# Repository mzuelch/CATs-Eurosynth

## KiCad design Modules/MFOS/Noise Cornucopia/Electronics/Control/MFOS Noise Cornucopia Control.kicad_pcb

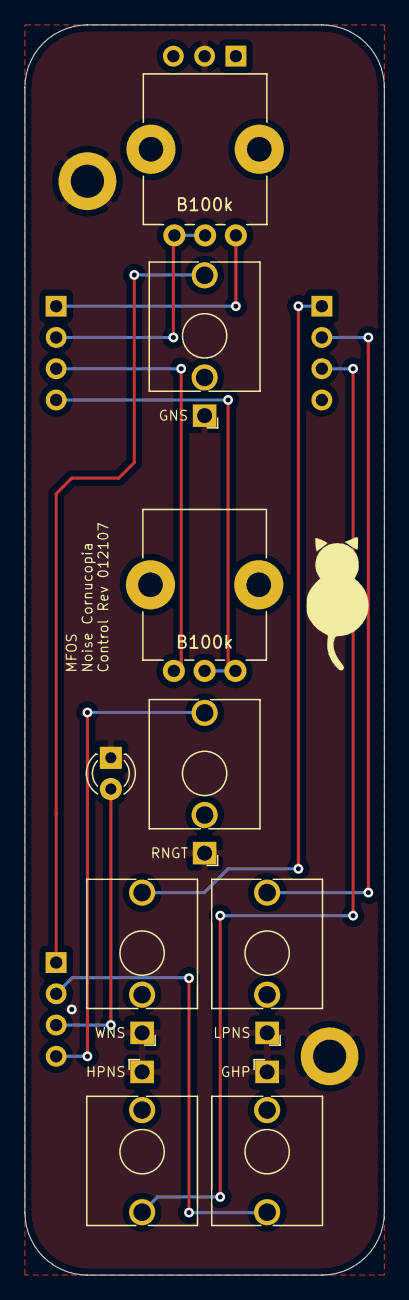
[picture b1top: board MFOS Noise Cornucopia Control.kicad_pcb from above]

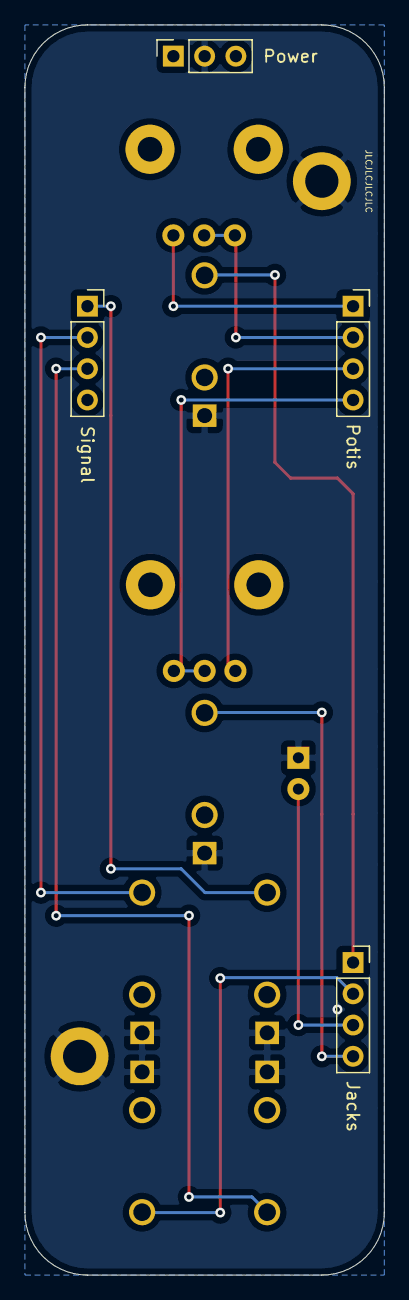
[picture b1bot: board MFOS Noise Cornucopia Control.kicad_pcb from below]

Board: 2 copper layers, 29.2 x 101.6 mm, 15 parts (4 on the bottom side), 12 nets.

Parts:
D1: LED; LED_D3.0mm
H1, H2: MountingHole_Pad; MountingHole_2.7mm_M2.5_DIN965_Pad
J1: WNS; Jack_3.5mm_QingPu_WQP-PJ398SM_Vertical_CircularHoles
J2: Power; PinSocket_1x03_P2.54mm_Vertical
J3: Signal; PinSocket_1x04_P2.54mm_Vertical
J4: LPNS; Jack_3.5mm_QingPu_WQP-PJ398SM_Vertical_CircularHoles
J5: HPNS; Jack_3.5mm_QingPu_WQP-PJ398SM_Vertical_CircularHoles
J6: Potis; PinSocket_1x04_P2.54mm_Vertical
J7: Jacks; PinSocket_1x04_P2.54mm_Vertical
J8: GNS; Jack_3.5mm_QingPu_WQP-PJ398SM_Vertical_CircularHoles
J9: GHP; Jack_3.5mm_QingPu_WQP-PJ398SM_Vertical_CircularHoles
J10: RNGT; Jack_3.5mm_QingPu_WQP-PJ398SM_Vertical_CircularHoles
R18, R28: B100k; Potentiometer_Alps_RK09K_Single_Vertical

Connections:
GHP: J7.2, J9.T
GND: D1.1, H1.1, H2.1, J1.S, J2.2, J4.S, J5.S, J8.S, J9.S, J10.S
GNS: J7.1, J8.T
GRNS1: J6.1, R18.1
GRNS2: J6.2, R18.2, R18.3
GTF1: J6.3, R28.3
GTF2: J6.4, R28.1, R28.2
HPNS: J3.3, J5.T
LEDA: D1.2, J7.3
LPNS: J3.2, J4.T
RNGT: J7.4, J10.T
WNS: J1.T, J3.1

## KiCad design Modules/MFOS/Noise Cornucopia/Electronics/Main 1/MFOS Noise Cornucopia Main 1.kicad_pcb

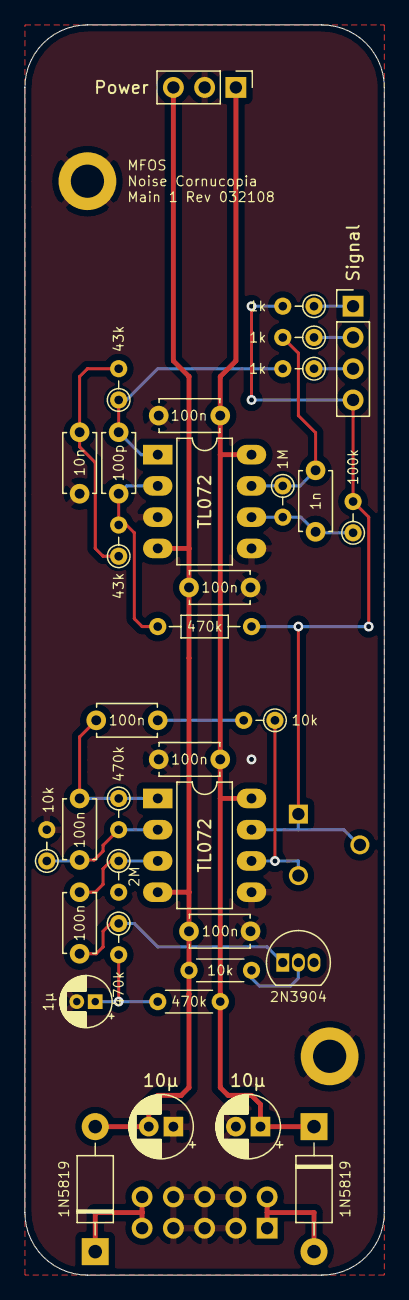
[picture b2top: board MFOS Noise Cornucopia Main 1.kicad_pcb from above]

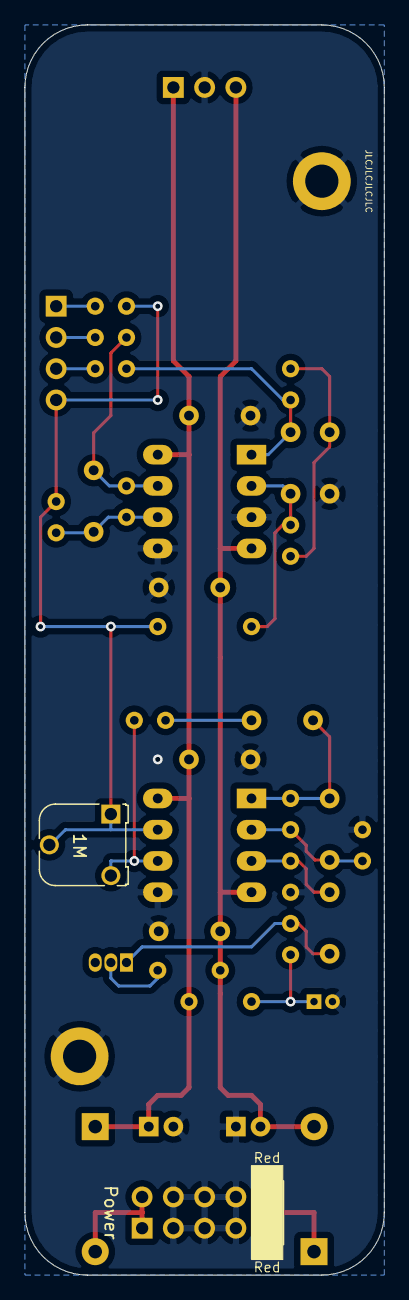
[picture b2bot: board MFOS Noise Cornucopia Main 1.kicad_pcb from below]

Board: 2 copper layers, 29.2 x 101.6 mm, 39 parts (2 on the bottom side), 22 nets.

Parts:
C1, C2, C4, C5, C7, C10, C12: 100n; C_Disc_D4.7mm_W2.5mm_P5.00mm
C3: 1n; C_Disc_D4.7mm_W2.5mm_P5.00mm
C6, C11: 10µ; CP_Radial_D5.0mm_P2.00mm
C9: 100p; C_Disc_D4.7mm_W2.5mm_P5.00mm
C14: 10n; C_Disc_D4.7mm_W2.5mm_P5.00mm
C18: 1µ; CP_Radial_D4.0mm_P1.50mm
D4, D5: 1N5819; D_DO-41_SOD81_P10.16mm_Horizontal
H1, H2: MountingHole_Pad; MountingHole_2.7mm_M2.5_DIN965_Pad
J1: Signal; PinHeader_1x04_P2.54mm_Vertical
J2: Power; PinHeader_1x03_P2.54mm_Vertical
J4: Power; Power_2x5_Vertical
Q1: 2N3904; TO-92_Inline
R1, R3, R11: 1k; R_Axial_DIN0204_L3.6mm_D1.6mm_P2.54mm_Vertical
R2, R10: 470k; R_Axial_DIN0204_L3.6mm_D1.6mm_P2.54mm_Vertical
R4: 2M; R_Axial_DIN0204_L3.6mm_D1.6mm_P2.54mm_Vertical
R5, R9: 10k; R_Axial_DIN0204_L3.6mm_D1.6mm_P2.54mm_Vertical
R6: 100k; R_Axial_DIN0204_L3.6mm_D1.6mm_P2.54mm_Vertical
R7: 1M; R_Axial_DIN0204_L3.6mm_D1.6mm_P2.54mm_Vertical
R8: 1M; Potentiometer_Runtron_RM-065_Vertical
R12: 470k; R_Axial_DIN0204_L3.6mm_D1.6mm_P7.62mm_Horizontal
R16, R17: 43k; R_Axial_DIN0204_L3.6mm_D1.6mm_P2.54mm_Vertical
R33: 470k; R_Axial_DIN0204_L3.6mm_D1.6mm_P5.08mm_Horizontal
R34: 10k; R_Axial_DIN0204_L3.6mm_D1.6mm_P5.08mm_Horizontal
U1, U2: TL072; DIP-8_W7.62mm_LongPads

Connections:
+12V: C5.2, C6.1, C7.2, D4.1, J2.1, R33.1, U1.8, U2.8
+12VA: D4.2, J4.+12V
-12V: C10.1, C11.2, C12.1, D5.2, J2.3, R34.2, U1.4, U2.4
-12VA: D5.1, J4.-12V
GND: C5.1, C6.2, C7.1, C10.2, C11.1, C12.2, C14.1, C18.2, H1.1, H2.1, J2.2, J4.GND, R4.2, R9.2, U1.5, U2.3, U2.5
HPNS: J1.3, R11.1
LPNS: J1.2, R3.1
NOISE_INT: J1.4, R1.2, R6.2, R8.1, R8.2, R12.2, U1.7
unnamed: C1.1, R4.1, U1.3
unnamed: C1.2, Q1.1, R2.1
unnamed: C2.1, R5.2
unnamed: C2.2, C4.1, R10.1, U1.1
unnamed: C3.1, R3.2, R7.1, U2.7
unnamed: C3.2, R6.1, R7.2, U2.6
unnamed: C4.2, R9.1, R10.2, U1.2
unnamed: C9.1, R12.1, R16.2, U2.2
unnamed: C9.2, R11.2, R17.1, U2.1
unnamed: C14.2, R16.1, R17.2
unnamed: C18.1, R2.2, R33.2
unnamed: Q1.2, R34.1
unnamed: R5.1, R8.3, U1.6
WNS: J1.1, R1.1

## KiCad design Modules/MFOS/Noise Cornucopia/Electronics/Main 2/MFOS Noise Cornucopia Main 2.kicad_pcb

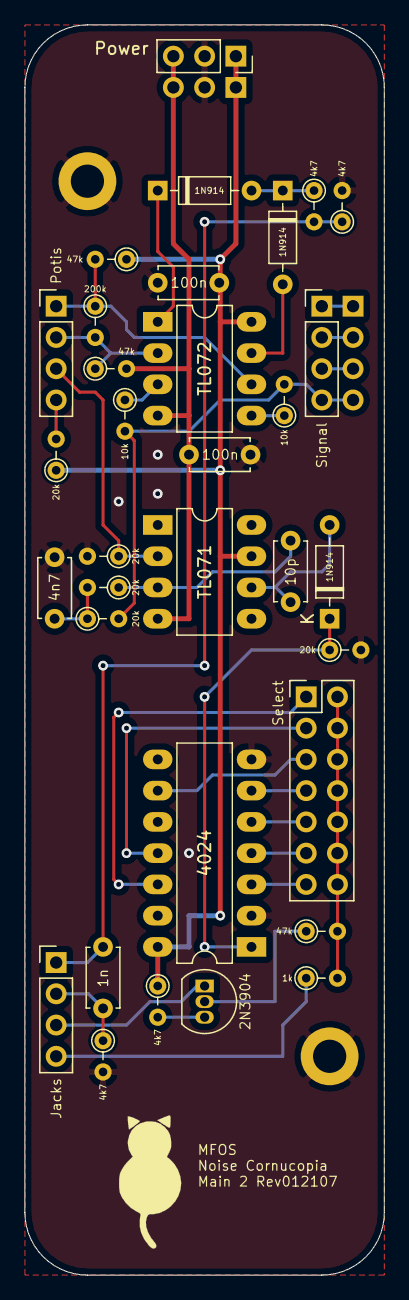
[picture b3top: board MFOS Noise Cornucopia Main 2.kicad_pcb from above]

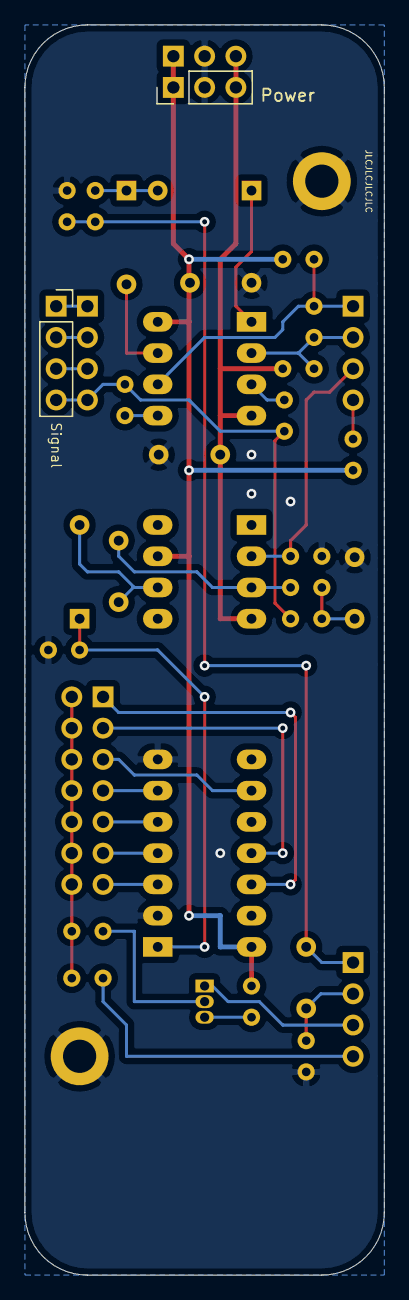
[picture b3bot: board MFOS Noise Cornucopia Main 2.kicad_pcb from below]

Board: 2 copper layers, 29.2 x 101.6 mm, 37 parts (2 on the bottom side), 34 nets.

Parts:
C8, C13: 100n; C_Disc_D4.7mm_W2.5mm_P5.00mm
C15: 1n; C_Disc_D4.7mm_W2.5mm_P5.00mm
C16: 10p; C_Disc_D4.7mm_W2.5mm_P5.00mm
C17: 4n7; C_Disc_D4.7mm_W2.5mm_P5.00mm
D1, D2, D3: 1N914; D_DO-35_SOD27_P7.62mm_Horizontal
H1, H2: MountingHole_Pad; MountingHole_2.7mm_M2.5_DIN965_Pad
J1: Select; PinHeader_2x07_P2.54mm_Vertical
J2: Power; PinSocket_1x03_P2.54mm_Vertical
J3: Signal; PinSocket_1x04_P2.54mm_Vertical
J4: Signal; PinHeader_1x04_P2.54mm_Vertical
J5: Power; PinHeader_1x03_P2.54mm_Vertical
J6: Potis; PinHeader_1x04_P2.54mm_Vertical
J7: Jacks; PinHeader_1x04_P2.54mm_Vertical
Q2: 2N3904; TO-92_Inline
R13, R22, R30: 47k; R_Axial_DIN0204_L3.6mm_D1.6mm_P2.54mm_Vertical
R14, R20: 10k; R_Axial_DIN0204_L3.6mm_D1.6mm_P2.54mm_Vertical
R15, R21, R23, R24: 4k7; R_Axial_DIN0204_L3.6mm_D1.6mm_P2.54mm_Vertical
R19: 200k; R_Axial_DIN0204_L3.6mm_D1.6mm_P2.54mm_Vertical
R25, R26, R27, R29, R31: 20k; R_Axial_DIN0204_L3.6mm_D1.6mm_P2.54mm_Vertical
R32: 1k; R_Axial_DIN0204_L3.6mm_D1.6mm_P2.54mm_Vertical
U3: TL072; DIP-8_W7.62mm_LongPads
U4: TL071; DIP-8_W7.62mm_LongPads
U5: 4024; DIP-14_W7.62mm_LongPads

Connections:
+12V: C8.2, J2.1, J5.1, R13.1, R24.1, R25.1, U3.8, U4.7, U5.14
-12V: C13.1, J2.3, J5.3, R22.2, U3.4, U4.4
GHP: C15.2, J7.2, R23.1
GND: C8.1, C13.2, C17.2, H1.1, H2.1, J2.2, J5.2, R21.2, R23.2, R29.2, R31.2, U5.2, U5.7
GNS: C15.1, J7.1, R15.2, R21.1
GRNS1: J6.1, R13.2, R19.1, U3.6
GRNS2: J6.2, R19.2, R22.1, U3.2
GTF1: J6.3, R31.1, U4.2
GTF2: J6.4, R25.2
LEDA: J7.3, Q2.1
NOISE_INT: J3.4, J4.4, R14.2, R20.2, R26.2
unnamed: C16.1, R27.1, U4.3
unnamed: C16.2, D3.2, U4.6
unnamed: C17.1, R26.1, R27.2
unnamed: D1.1, D2.2, R15.1
unnamed: D1.2, U3.7
unnamed: D2.1, U3.1
unnamed: D3.1, R29.1, U5.1
unnamed: J1.1, U5.12
unnamed: J1.3, U5.11
unnamed: J1.5, U5.9
unnamed: J1.7, U5.6
unnamed: J1.9, U5.5
unnamed: J1.2, J1.4, J1.6, J1.8, J1.10, J1.12, J1.14, R30.2, R32.2
unnamed: J1.11, U5.4
unnamed: J1.13, U5.3
unnamed: J3.1, J4.1
unnamed: J3.2, J4.2
unnamed: J3.3, J4.3
unnamed: Q2.2, R30.1
unnamed: Q2.3, R24.2
unnamed: R14.1, U3.5
unnamed: R20.1, U3.3
RNGT: J7.4, R32.1

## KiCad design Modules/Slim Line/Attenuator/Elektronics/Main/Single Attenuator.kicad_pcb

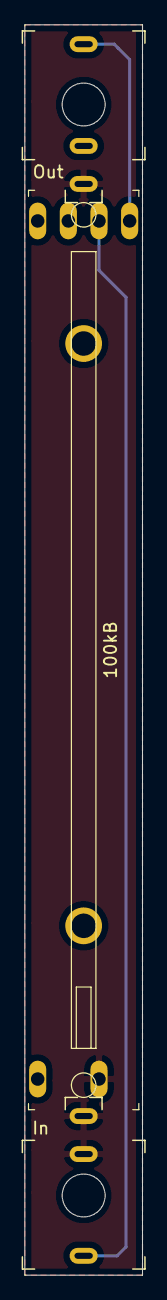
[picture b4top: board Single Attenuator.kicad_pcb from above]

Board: 2 copper layers, 9.6 x 102.0 mm, 3 parts (0 on the bottom side), 3 nets.

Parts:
J1: In; PJ-301-M-12
J2: Out; PJ-301-M-12
RV1: 100kB; Potentiometer_Fader_Alps_RS__01_Dual

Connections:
GND: J1.S, J1.TN, J2.S, RV1.3
unnamed: J1.T, RV1.1
unnamed: J2.T, RV1.2
